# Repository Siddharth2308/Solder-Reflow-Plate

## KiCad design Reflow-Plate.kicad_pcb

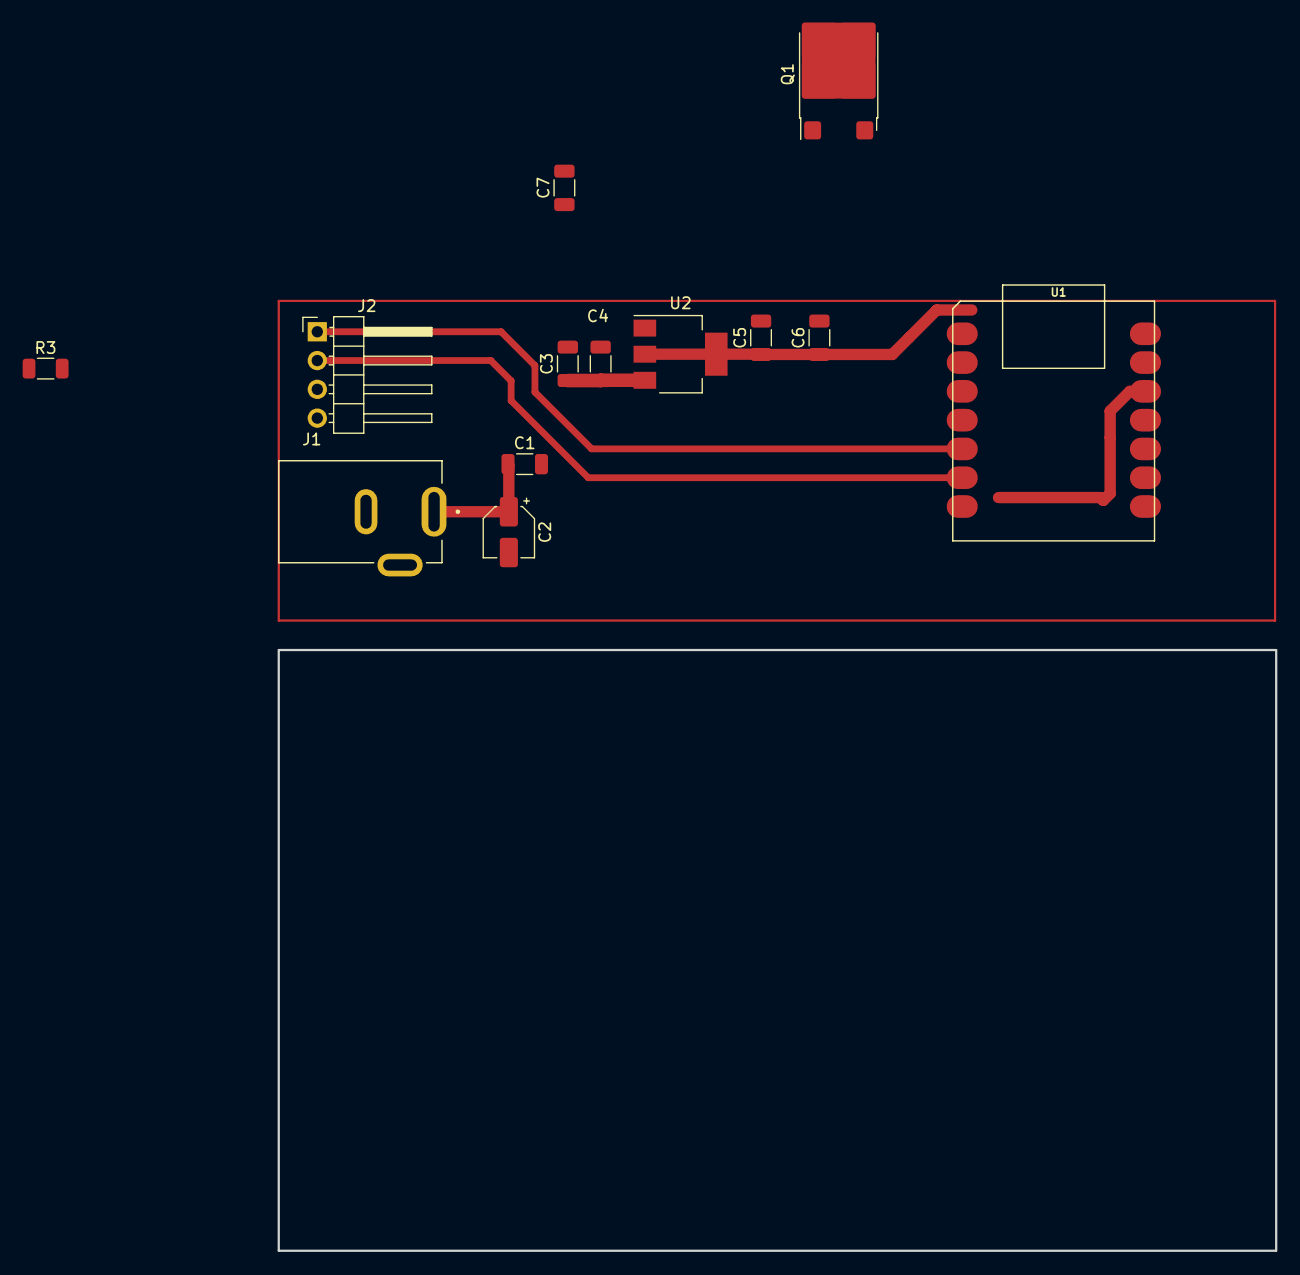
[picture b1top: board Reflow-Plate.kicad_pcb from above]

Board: 2 copper layers, 88.0 x 53.0 mm, 13 parts (0 on the bottom side), 7 nets.

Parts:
C1, C4, C6: 100nF; C_1206_3216Metric
C2: 100uF; CP_Elec_4x4.5
C3, C5: 22uF; C_1206_3216Metric
C7: 1nF; C_1206_3216Metric
J1: DC-005-5A-2.0; XKB_DC-005-5A-2.0
J2: Conn_01x04_Pin; PinHeader_1x04_P2.54mm_Horizontal
Q1: NMOS; ATPAK-2
R3: R; R_1206_3216Metric
U1: MOUDLE-SEEEDUINO-XIAO-ESP32S3; MOUDLE14P-SMD-2.54-21X17.8MM
U2: AMS1117-3.3; SOT-223-3_TabPin2

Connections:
+3V3: C5.1, C6.1, J2.3, U1.12 (3V3), U2.2 (VO)
GNDREF: C1.2, C2.2, C3.2, C4.2, C5.2, C6.2, J1.2, J1.3, J2.4, Q1.3 (S), R3.2, U1.13 (GND), U2.1 (GND)
Gate: Q1.2 (G), R3.1
Heating Element: C1.1, C2.1, C7.1, C7.2, J1.1, Q1.1 (D)
SCL: J2.2, U1.6 (PA9_A5_D5_SCL)
SDA: J2.1, U1.5 (PA8_A4_D4_SDA)
VDC: C3.1, C4.1, U2.3 (VI)

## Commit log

2024-03-04 Init
2024-03-04 Suiii
